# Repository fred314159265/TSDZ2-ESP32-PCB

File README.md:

# Alternative TSDZ2-ESP32 Bluetooth PCB

⚠⚠⚠ This is current untested - not fit for use *yet*! ⚠⚠⚠

This repository is an updated version of MSpider65's [TSDZ2-ESP32-PCB](https://github.com/TSDZ2-ESP32/TSDZ2-ESP32-PCB) project. If you are not familiar with the original project, it is a PCB and some custom firmware (plus Android app) that make the TSDZ2 eBike mid-drive kit smarter (fully customisable settings, log power, speed, etc.) and higher performance. It's a really fantastic project and definitely worth checking out if you're considering the TSDZ2 eBike mid-drive kit.

For more information on the project, see Mspider65's wiki page: [wiki.](https://github.com/TSDZ-ESP32/TSDZ-ESP32-wiki/wiki)

This update aims to make it more affordable (~$12 vs ~$23 for components). It also aims to use components that are generally slightly easier to solder by hand. It has been done in [KiCAD](https://www.kicad.org), ensuring full control of the source design files.

## Changes

- All connector are now 0.1" pin headers. The intention for these (except the programming connector) is to directly solder the TSDZ2's wires to these as pads instead of actually using pin headers. Being 0.1", some connectors (JST XH?) will also fit, and you are welcome to use as desired.

- 5V and 3.3V regulator changes - cost savings.

- Programming header now uses RST and GPIO0 pins directly (no need for jumpers), with the intention of using RTS and CTS lines of a USB-to-serial adaptor to automate putting the ESP32 in bootloader mode. More information can be found [here](https://github.com/espressif/esptool/wiki/ESP32-Boot-Mode-Selection#automatic-bootloader).
  
  TLDR: connect RST and GPIO0 pins to USB-to-serial adaptor like so, and programming should "just work". 
  
  ⚠ **Make sure you only power the board via 3.3V!** ⚠
  
  | Programming Header Pin | USB-to-serial Pin |
  | ---------------------- | ----------------- |
  | RST                    | RTS               |
  | IO0                    | DTR               |
  
- Temperature sensor changed to much cheaper and also lower spec device. (Cause for firmware update.) Still is plenty accurate enough for monitoring PCB temperature and is much cheaper.

- Added solder bridge pads - removes need for diode. Make sure you bridge these with a soldering iron after programming the ESP32.

- Programming header is on breakoff part of board.

- Redrawn from scratch in KiCAD.

## Pinout

## FAQs

#### Why not use MSpider65's original PCB design?

I have use the original design and it works very well. After needing another PCB recently I saw that many of the components have become very expensive (general silicon shortage at this time...). This updated board aims to be much cheaper while having the same functionality and remaining the same size. This will require an update to the ESP32's firmware, but this should be a small change.

#### What's with the bit of the PCB sticking out?

This is for programming the ESP32 with a USB-to-serial adaptor. Once the ESP32 has been programmed, cut the tracks on the top and the bottom with a knife and then snap it off. MSpider65's project allows OTA (over-the-air) firmware updates so you won't be needing it again.

#### I successfully programmed the ESP32 but the board won't turn on when connected to battery power?

After programming, you need to short JP1 & JP2 on the PCB with a soldering iron. This is instead of using a diode in the design. (Slight cost saving and more efficient.) A trade-off I personally like in this case. Let me know if you prefer a diode...

#### Why is there a USB-to-Serial adaptor in the BOM?

As part of the aim to keep cost to a minimum, all items can be sourced from [LCSC](https://lcsc.com). Both the USB-to-serial adaptors and 2.4GHz antenna are quite inexpensive from LCSC and so have been included in the BOM for convenience. Of course if you are making more than one board you only require one USB-to-serial adaptor, but multiple antennas.

#### How can I order the PCB?

You can order the bare PCB from [JLCPCB](https://jlcpcb.com). You will need to select 4-layers, 0.8mm thickness and "JLC7629" controlled impedance. I also recommend getting a stencil and using solder paste. 

Example of suitable PCB options:

#### How can I order the components?

Upload "TSDZ2-ESP32-Alt_BOM.csv" to the "BOM tool" on LCSC [here](https://lcsc.com/bom.html#/upload). Only select quantity and part number columns. Be sure to adjust how many USB-to-serial adaptors you require before checking out. Also note that currently if you order the PCB before the components (from JLCPCB) you can get a discount on postage with LCSC at checkout.

#### How did you curve tracks/add teardrops?

By using the [KiCAD round tracks](https://github.com/mitxela/kicad-round-tracks) and [teardrops](https://github.com/NilujePerchut/kicad_scripts/tree/master/teardrops) plugins.

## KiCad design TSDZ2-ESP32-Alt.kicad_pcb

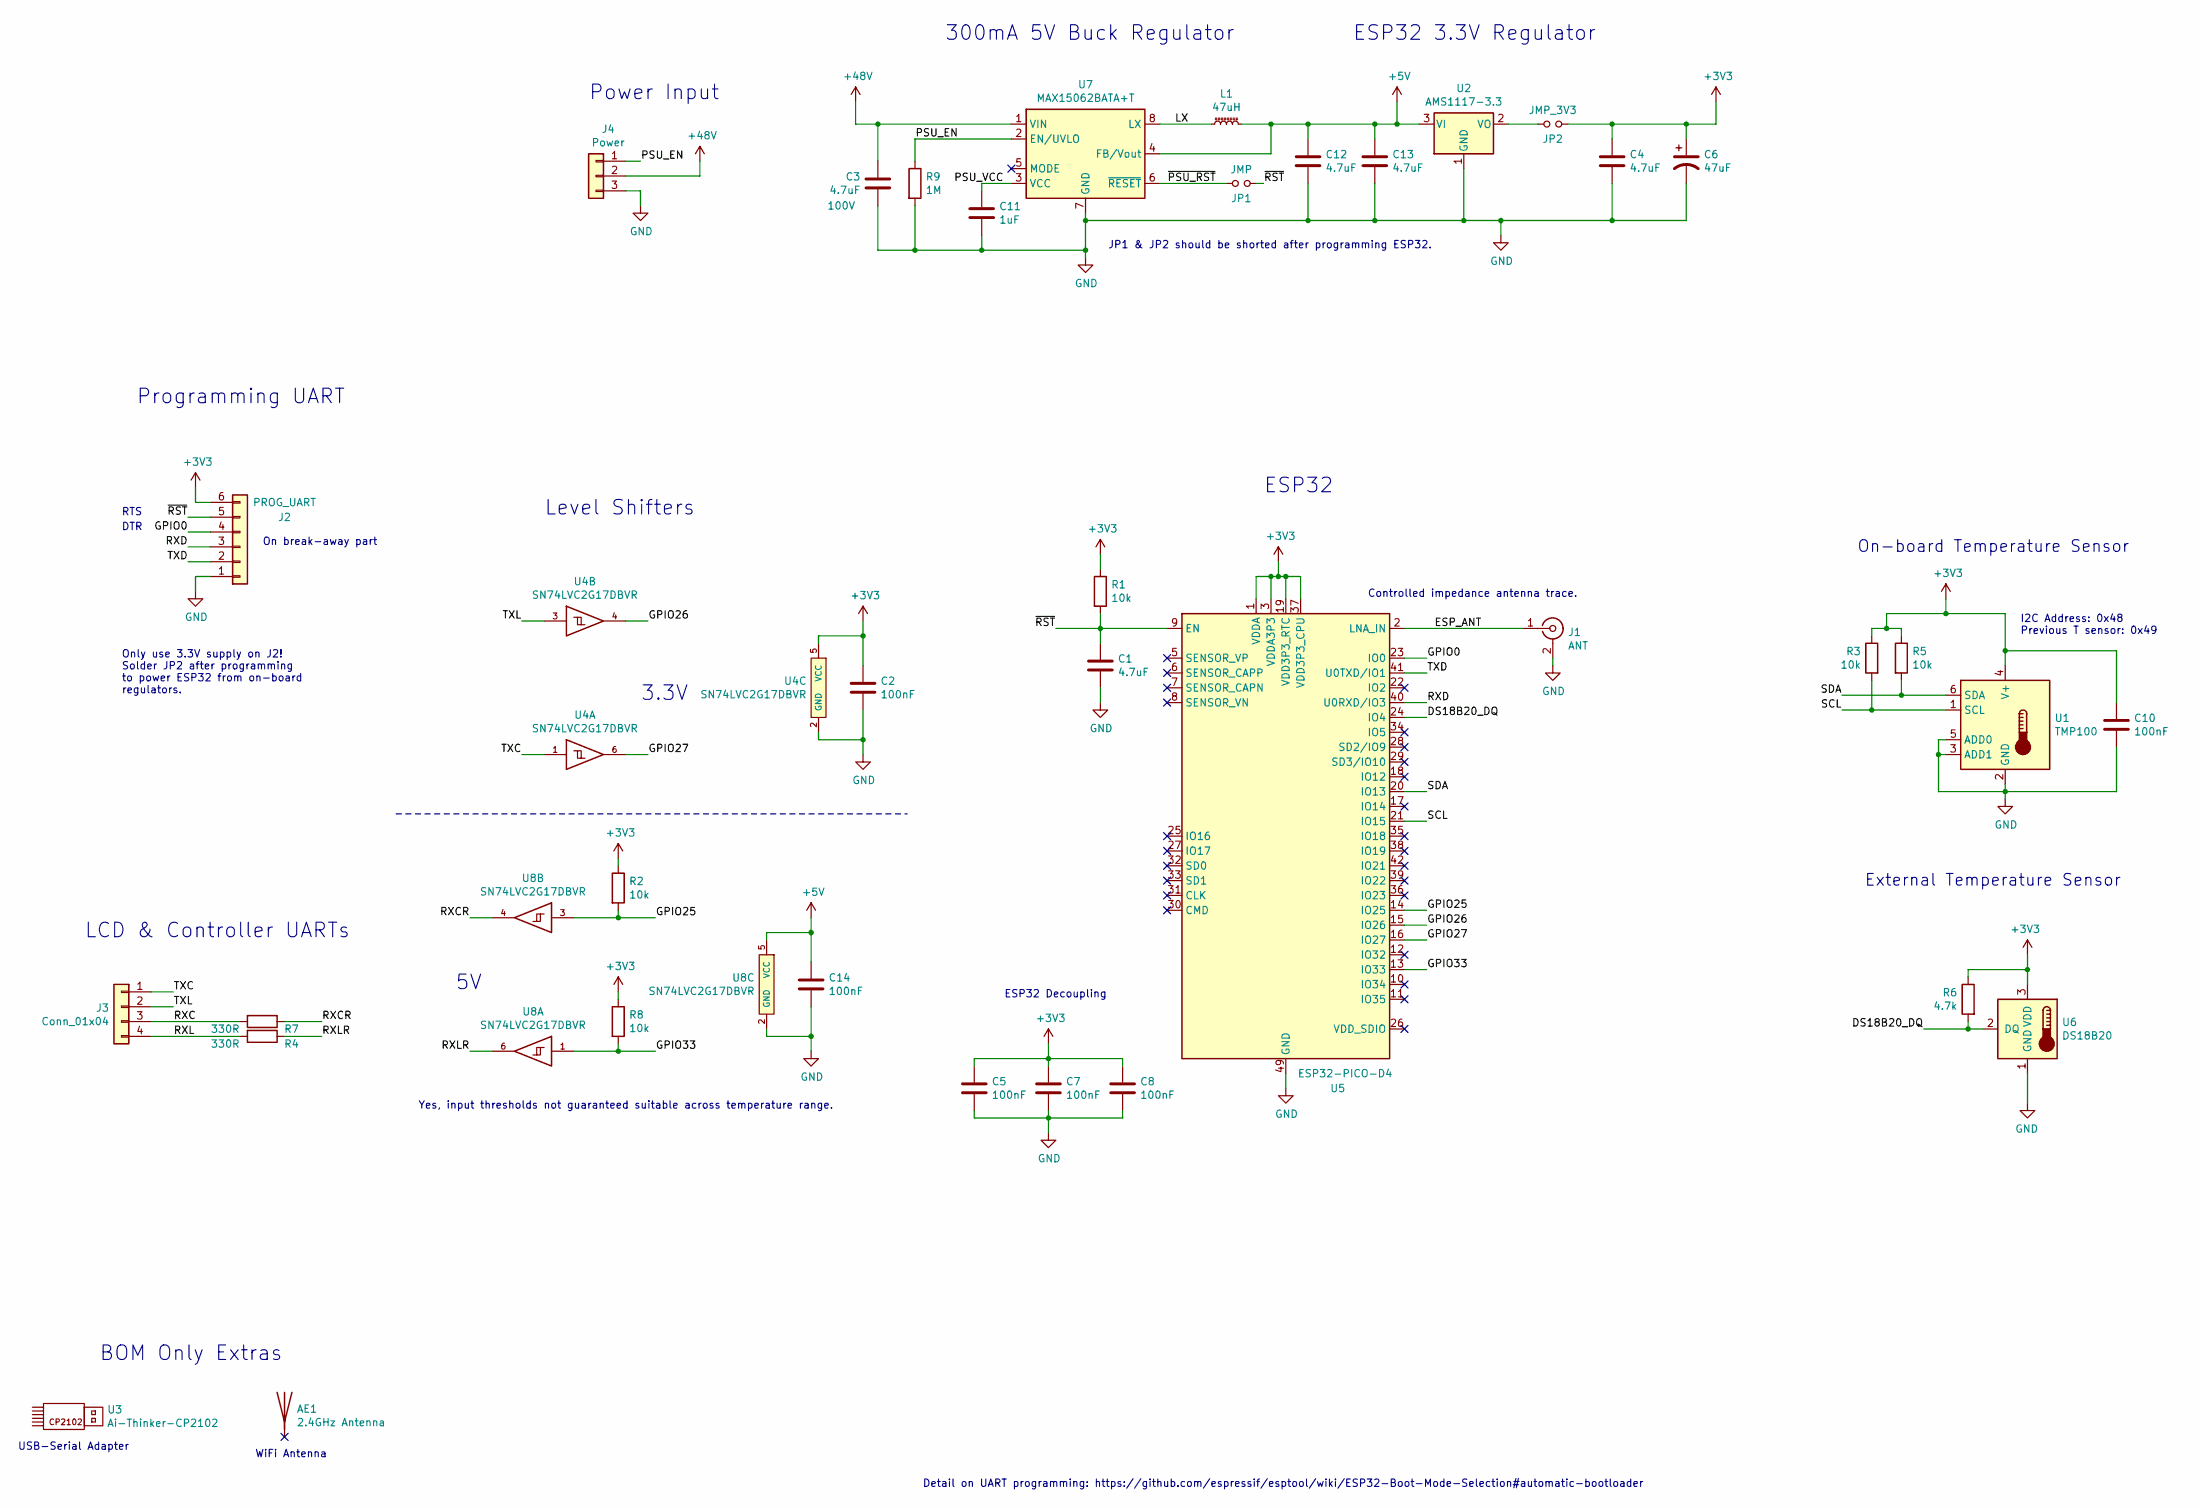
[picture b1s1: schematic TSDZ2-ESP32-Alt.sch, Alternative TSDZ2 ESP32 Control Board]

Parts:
AE1: 2.4GHz Antenna; LCSC Part # C209923
C1, C4, C12, C13: 4.7uF; C_0805_2012Metric_Pad1.15x1.40mm_HandSolder; LCSC Part # C98195
C2, C5, C7, C8, C10, C14: 100nF; C_0603_1608Metric_Pad1.05x0.95mm_HandSolder; LCSC Part # C14663
C3: 4.7uF; C_1210_3225Metric; Voltage 100V; LCSC Part # C697607
C6: 47uF; CP_EIA-3528-21_Kemet-B_Pad1.50x2.35mm_HandSolder; LCSC Part # C116617
C11: 1uF; C_0603_1608Metric_Pad1.05x0.95mm_HandSolder; LCSC Part # C59782
J1: ANT; U.FL-R-SMT-1(80); LCSC Part # C88374
J2: PROG_UART; PinHeader_1x06_P2.54mm_Vertical
J3: Conn_01x04; PinHeader_1x04_P2.54mm_Vertical
J4: Power; PinHeader_1x03_P2.54mm_Vertical
JP1: JMP; SolderJumper-2_P1.3mm_Open_RoundedPad1.0x1.5mm
JP2: JMP_3V3; SolderJumper-2_P1.3mm_Open_RoundedPad1.0x1.5mm
L1: 47uH; L_Bourns-SRN6028; LCSC Part # C497831
R1, R2, R3, R5, R8: 10k; R_0603_1608Metric_Pad0.98x0.95mm_HandSolder; LCSC Part # C25804
R4, R7: 330R; R_0603_1608Metric_Pad0.98x0.95mm_HandSolder; LCSC Part # C23138
R6: 4.7k; R_0603_1608Metric_Pad0.98x0.95mm_HandSolder; LCSC Part # C25999
R9: 1M; R_0603_1608Metric_Pad0.98x0.95mm_HandSolder; LCSC Part # C26098
U1: TMP100; SOT-23-6_Handsoldering; LCSC Part # C31810
U2: AMS1117-3.3; SOT-223-3_TabPin2; LCSC Part # C6186
U3: Ai-Thinker-CP2102; LCSC Part # C192392
U4, U8: SN74LVC2G17DBVR; SOT-23-6_Handsoldering; LCSC Part # C10429
U5: ESP32-PICO-D4; QFN-48-1EP_7x7mm_P0.5mm_EP5.3x5.3mm; LCSC Part # C193707
U6: DS18B20; PinHeader_1x03_P2.54mm_Vertical; LCSC Part # C376006
U7: MAX15062BATA+T; DFN-8_2x2mm_P0.5mm; LCSC Part # C143362

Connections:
+3V3: C2.1, C4.1, C5.1, C6.1, C7.1, C8.1, C10.1, J2.6, JP2.2, R1.1, R2.1, R3.1, R5.1, R6.1, R8.1, U1.4 (V+), U4.5 (VCC), U5.1 (VDDA), U5.3 (VDDA3P3), U5.4 (VDDA3P3), U5.19 (VDD3P3_RTC), U5.37 (VDD3P3_CPU), U5.43 (VDDA), U5.46 (VDDA), U6.3 (VDD)
+5V: C12.1, C13.1, C14.1, L1.2, U2.3 (VI), U7.4 (FB/Vout), U8.5 (VCC)
+48V: C3.1, J4.2, U7.1 (VIN)
/DS18B20_DQ: R6.2, U5.24 (IO4), U6.2 (DQ)
/ESP_ANT: J1.1 (In), U5.2 (LNA_IN)
/GPIO0: J2.4, U5.23 (IO0)
/GPIO25: R2.2, U5.14 (IO25), U8.3
/GPIO26: U4.4, U5.15 (IO26)
/GPIO27: U4.6, U5.16 (IO27)
/GPIO33: R8.2, U5.13 (IO33), U8.1
/LX: L1.1, U7.8 (LX)
/PSU_EN: J4.1, R9.1, U7.2 (EN/UVLO)
/PSU_VCC: C11.1, U7.3 (VCC)
/RXC: J3.3, R7.2
/RXCR: R7.1, U8.4
/RXD: J2.3, U5.40 (U0RXD/IO3)
/RXL: J3.4, R4.2
/RXLR: R4.1, U8.6
/SCL: R3.2, U1.1 (SCL), U5.21 (IO15)
/SDA: R5.2, U1.6 (SDA), U5.20 (IO13)
/TXC: J3.1, U4.1
/TXD: J2.2, U5.41 (U0TXD/IO1)
/TXL: J3.2, U4.3
/~PSU_RST: JP1.1, U7.6 (~RESET)
/~RST: C1.1, J2.5, JP1.2, R1.2, U5.9 (EN)
GND: C1.2, C2.2, C3.2, C4.2, C5.2, C6.2, C7.2, C8.2, C10.2, C11.2, C12.2, C13.2, C14.2, J1.2 (Ext), J2.1, J4.3, R9.2, U1.2 (GND), U1.3 (ADD1), U1.5 (ADD0), U2.1 (GND), U4.2 (GND), U5.49 (GND), U6.1 (GND), U7.7 (GND), U8.2 (GND)
unnamed: JP2.1, U2.2 (VO)

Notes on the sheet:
Controlled impedance antenna trace.
Level Shifters
BOM Only Extras
ESP32 Decoupling
External Temperature Sensor
On-board Temperature Sensor
I2C Address: 0x48 Previous T sensor: 0x49
ESP32 3.3V Regulator
300mA 5V Buck Regulator
Power Input
WiFi Antenna
USB-Serial Adapter
ESP32
3.3V
LCD & Controller UARTs
Detail on UART programming: https://github.com/espressif/esptool/wiki/ESP32-Boot-Mode-Selection#automatic-bootloader
Programming UART
JP1 & JP2 should be shorted after programming ESP32.
DTR
RTS
On break-away part
Only use 3.3V supply on J2! Solder JP2 after programming to power ESP32 from on-board regulators.
Yes, input thresholds not guaranteed suitable across temperature range.

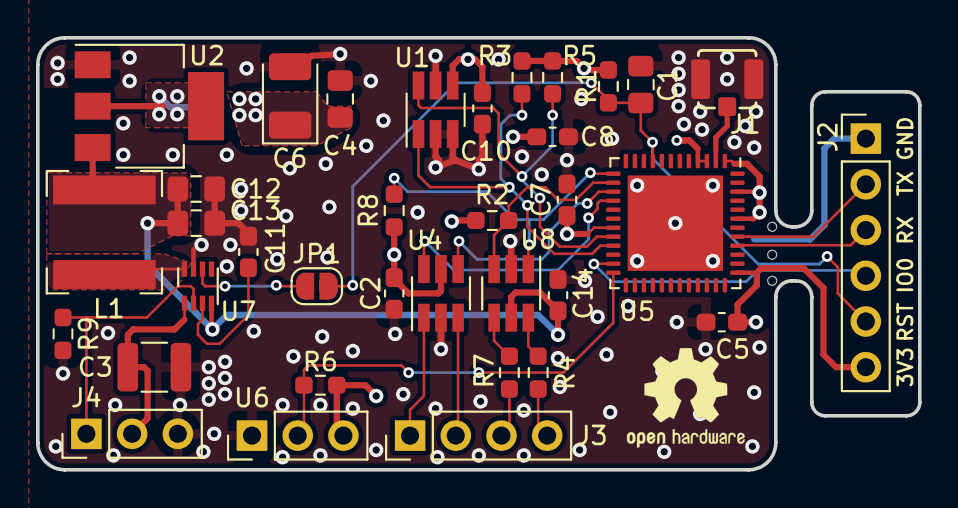
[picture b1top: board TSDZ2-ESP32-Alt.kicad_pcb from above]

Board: 4 copper layers, 49.0 x 24.0 mm, 36 parts (1 on the bottom side), 27 nets.

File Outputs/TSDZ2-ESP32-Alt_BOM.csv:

Item,Qty,Reference(s),Value,LibPart,Footprint,Datasheet,LCSC Part #,Voltage
1,1,AE1,2.4GHz Antenna,Device:Antenna,,https://datasheet.lcsc.com/lcsc/1912111437_HI-LINK-HLK-TX-PC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,C209923,
2,4,"C1, C4, C12, C13",4.7uF,Device:C,Capacitor_SMD:C_0805_2012Metric_Pad1.15x1.40mm_HandSolder,~,C98195,
3,6,"C2, C5, C7, C8, C10, C14",100nF,Device:C,Capacitor_SMD:C_0603_1608Metric_Pad1.05x0.95mm_HandSolder,~,C14663,
4,1,C3,4.7uF,Device:C,Capacitor_SMD:C_1210_3225Metric,https://datasheet.lcsc.com/lcsc/2007091536_Taiyo-Yuden-HMK32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,C697607,100V
5,1,C6,47uF,Device:CP1,Capacitor_Tantalum_SMD:CP_EIA-3528-21_Kemet-B_Pad1.50x2.35mm_HandSolder,~,C116617,
6,1,C11,1uF,Device:C,Capacitor_SMD:C_0603_1608Metric_Pad1.05x0.95mm_HandSolder,~,C59782,
7,1,J1,ANT,Connector:Conn_Coaxial,TSDZ2-ESP32-Alt:U.FL-R-SMT-1(80),https://datasheet.lcsc.com/lcsc/1811091710_HRS-Hirose-U-FL-R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,C88374,
8,1,J2,PROG_UART,Connector_Generic:Conn_01x06,Connector_PinHeader_2.54mm:PinHeader_1x06_P2.54mm_Vertical,~,,
9,1,J3,Conn_01x04,Connector_Generic:Conn_01x04,Connector_PinHeader_2.54mm:PinHeader_1x04_P2.54mm_Vertical,~,-,
10,1,J4,Power,Connector_Generic:Conn_01x03,Connector_PinHeader_2.54mm:PinHeader_1x03_P2.54mm_Vertical,~,-,
11,1,JP1,JMP,Device:Jumper_NO_Small,Jumper:SolderJumper-2_P1.3mm_Open_RoundedPad1.0x1.5mm,~,-,
12,1,JP2,JMP_3V3,Device:Jumper_NO_Small,Jumper:SolderJumper-2_P1.3mm_Open_RoundedPad1.0x1.5mm,~,-,
13,1,L1,47uH,Device:L_Core_Ferrite_Small,Inductor_SMD:L_Bourns-SRN6028,https://datasheet.lcsc.com/lcsc/2003172236_YJYCOIN-YNR6028-4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,C497831,
14,5,"R1, R2, R3, R5, R8",10k,Device:R,Resistor_SMD:R_0603_1608Metric_Pad0.98x0.95mm_HandSolder,~,C25804,
15,2,"R4, R7",330R,Device:R,Resistor_SMD:R_0603_1608Metric_Pad0.98x0.95mm_HandSolder,~,C23138,
16,1,R6,4.7k,Device:R,Resistor_SMD:R_0603_1608Metric_Pad0.98x0.95mm_HandSolder,~,C25999,
17,1,R9,1M,Device:R,Resistor_SMD:R_0603_1608Metric_Pad0.98x0.95mm_HandSolder,~,C26098,
18,1,U1,TMP100,Sensor_Temperature:TMP100,Package_TO_SOT_SMD:SOT-23-6_Handsoldering,http://www.ti.com/lit/gpn/tmp100,C31810,
19,1,U2,AMS1117-3.3,Regulator_Linear:AMS1117-3.3,Package_TO_SOT_SMD:SOT-223-3_TabPin2,http://www.advanced-monolithic.com/pdf/ds1117.pdf,C6186,
20,1,U3,Ai-Thinker-CP2102,TSDZ2-ESP32-Alt:Ai-Thinker-CP2102,,https://datasheet.lcsc.com/lcsc/Ai-Thinker-CP2102_C192392.pdf,C192392,
21,2,"U4, U8",SN74LVC2G17DBVR,TSDZ2-ESP32-Alt:SN74LVC2G17DBVR,Package_TO_SOT_SMD:SOT-23-6_Handsoldering,https://datasheet.lcsc.com/lcsc/Texas-Instruments-TI-SN74LVC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,C10429,
22,1,U5,ESP32-PICO-D4,RF_Module:ESP32-PICO-D4,Package_DFN_QFN:QFN-48-1EP_7x7mm_P0.5mm_EP5.3x5.3mm,https://www.espressif.com/sites/default/files/documentation/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,C193707,
23,1,U6,DS18B20,Sensor_Temperature:DS18B20,Connector_PinHeader_2.54mm:PinHeader_1x03_P2.54mm_Vertical,http://datasheets.maximintegrated.com/en/ds/DS18B20.pdf,C376006,
24,1,U7,MAX15062BATA+T,Regulator_Switching:MAX15062B,Package_DFN_QFN:DFN-8_2x2mm_P0.5mm,http://datasheets.maximintegrated.com/en/ds/MAX15062.pdf,C143362,

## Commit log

2021-05-08 Initial alternative version of PCB release.
2021-05-20 Fixed typos in README.
2021-05-22 Added interactive BOM file.
